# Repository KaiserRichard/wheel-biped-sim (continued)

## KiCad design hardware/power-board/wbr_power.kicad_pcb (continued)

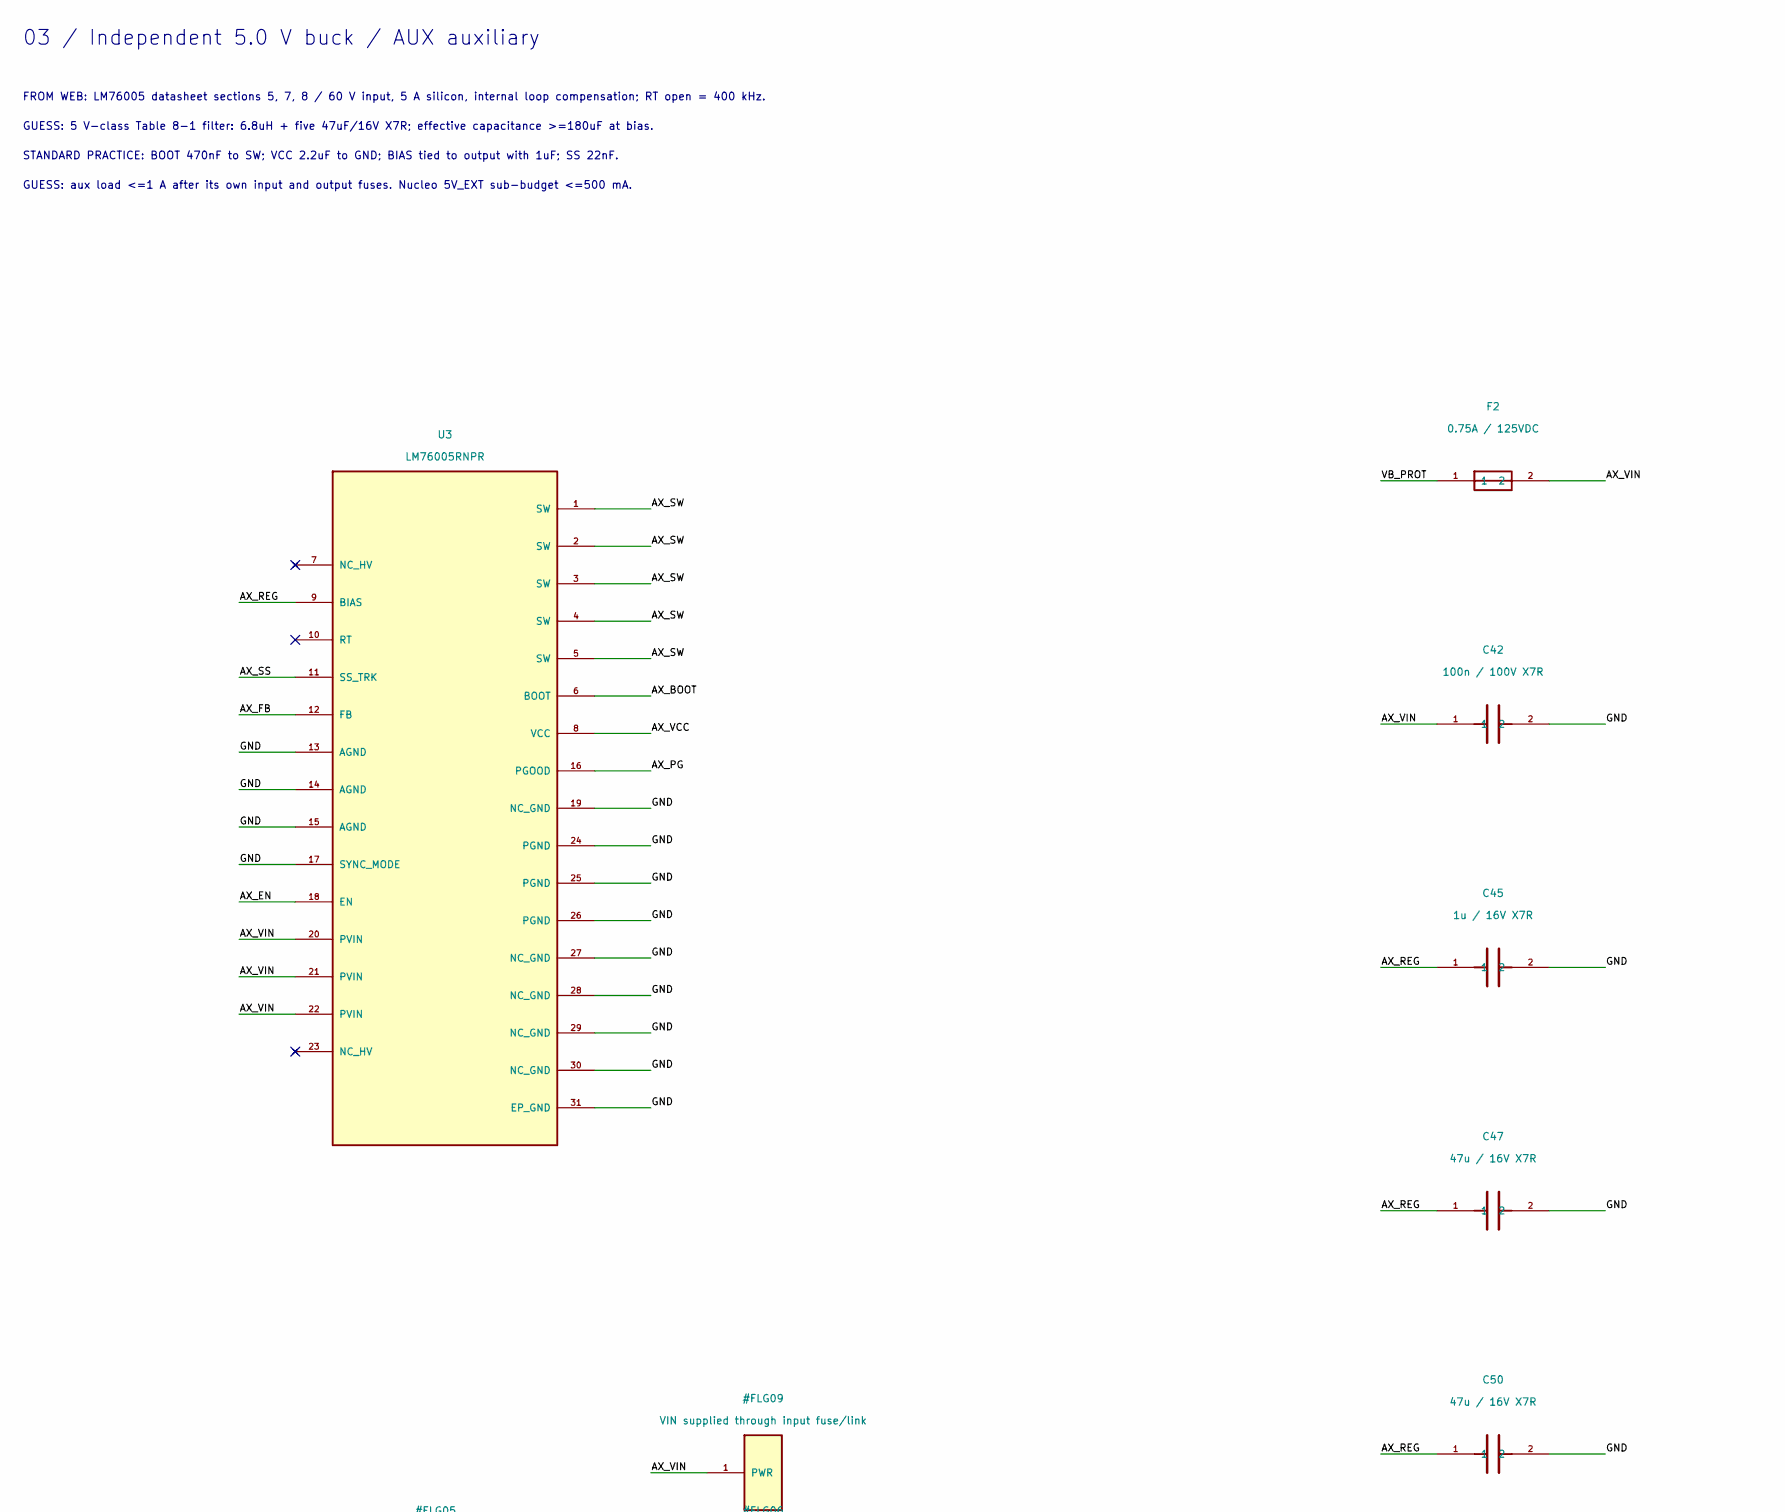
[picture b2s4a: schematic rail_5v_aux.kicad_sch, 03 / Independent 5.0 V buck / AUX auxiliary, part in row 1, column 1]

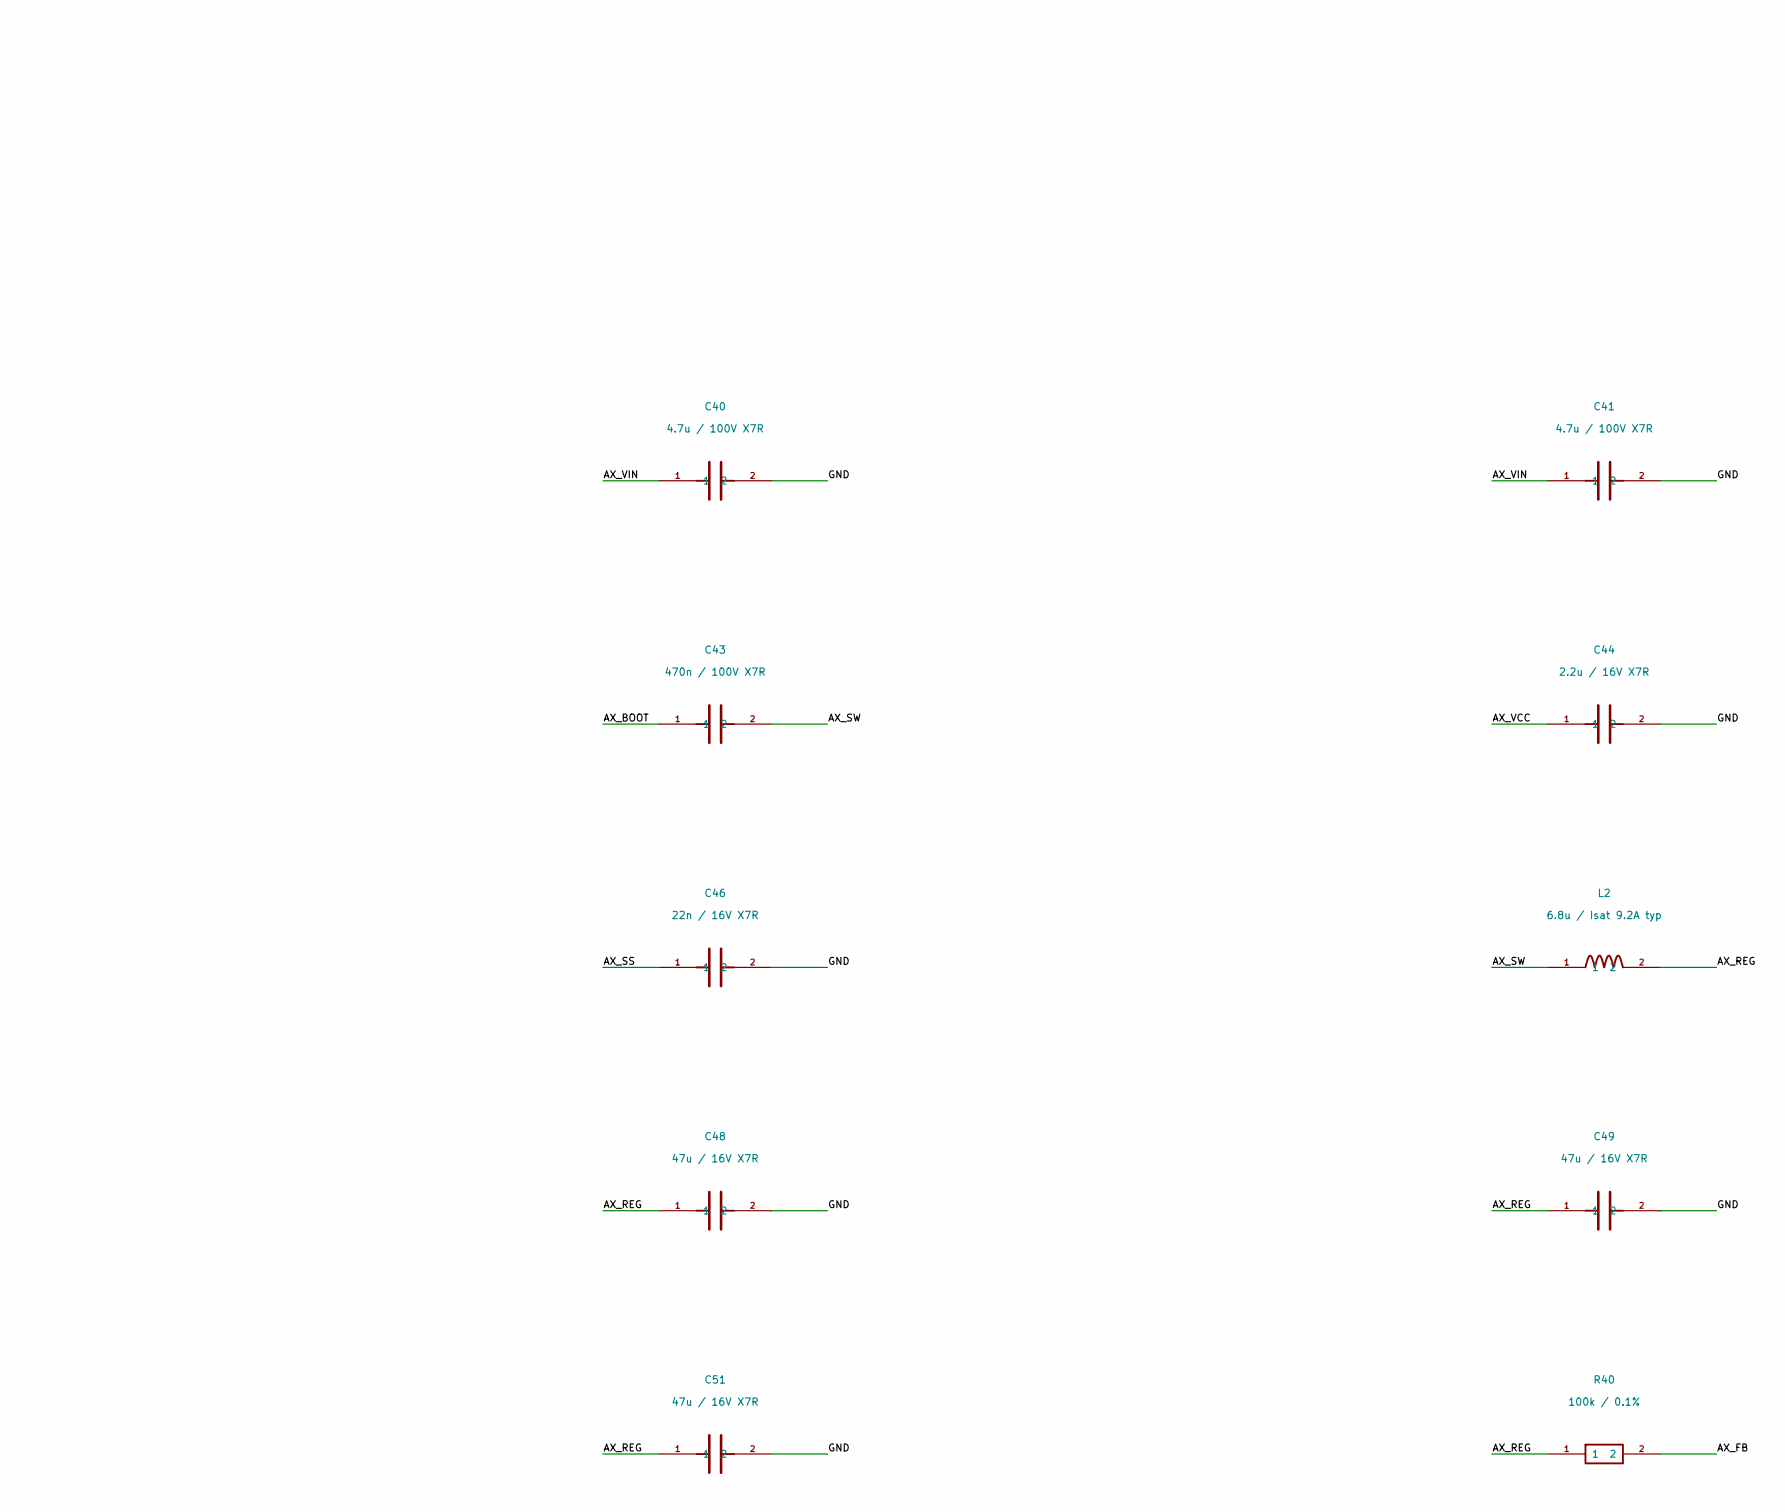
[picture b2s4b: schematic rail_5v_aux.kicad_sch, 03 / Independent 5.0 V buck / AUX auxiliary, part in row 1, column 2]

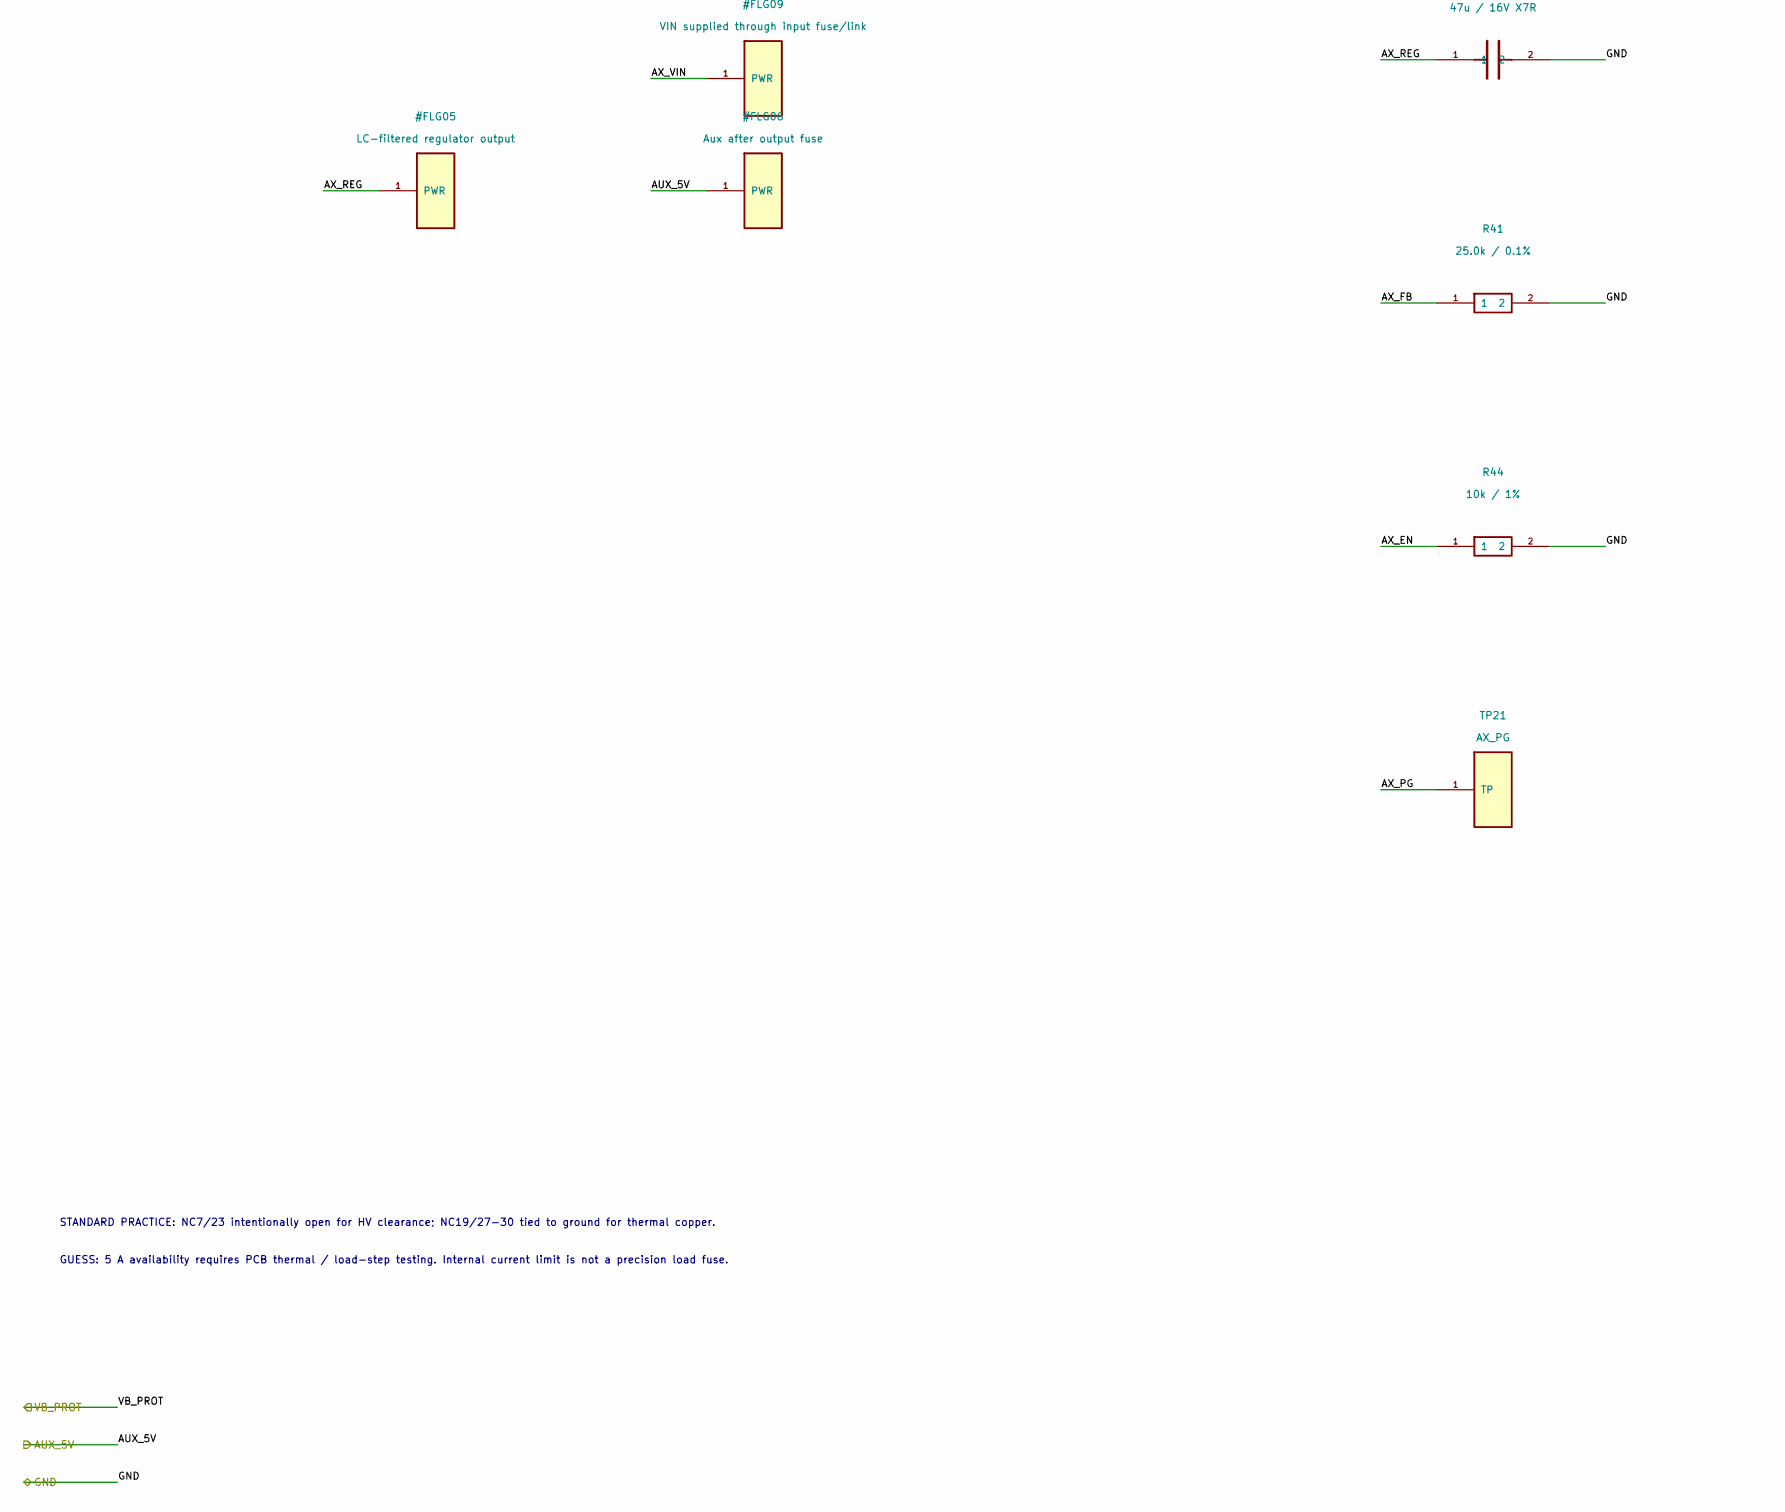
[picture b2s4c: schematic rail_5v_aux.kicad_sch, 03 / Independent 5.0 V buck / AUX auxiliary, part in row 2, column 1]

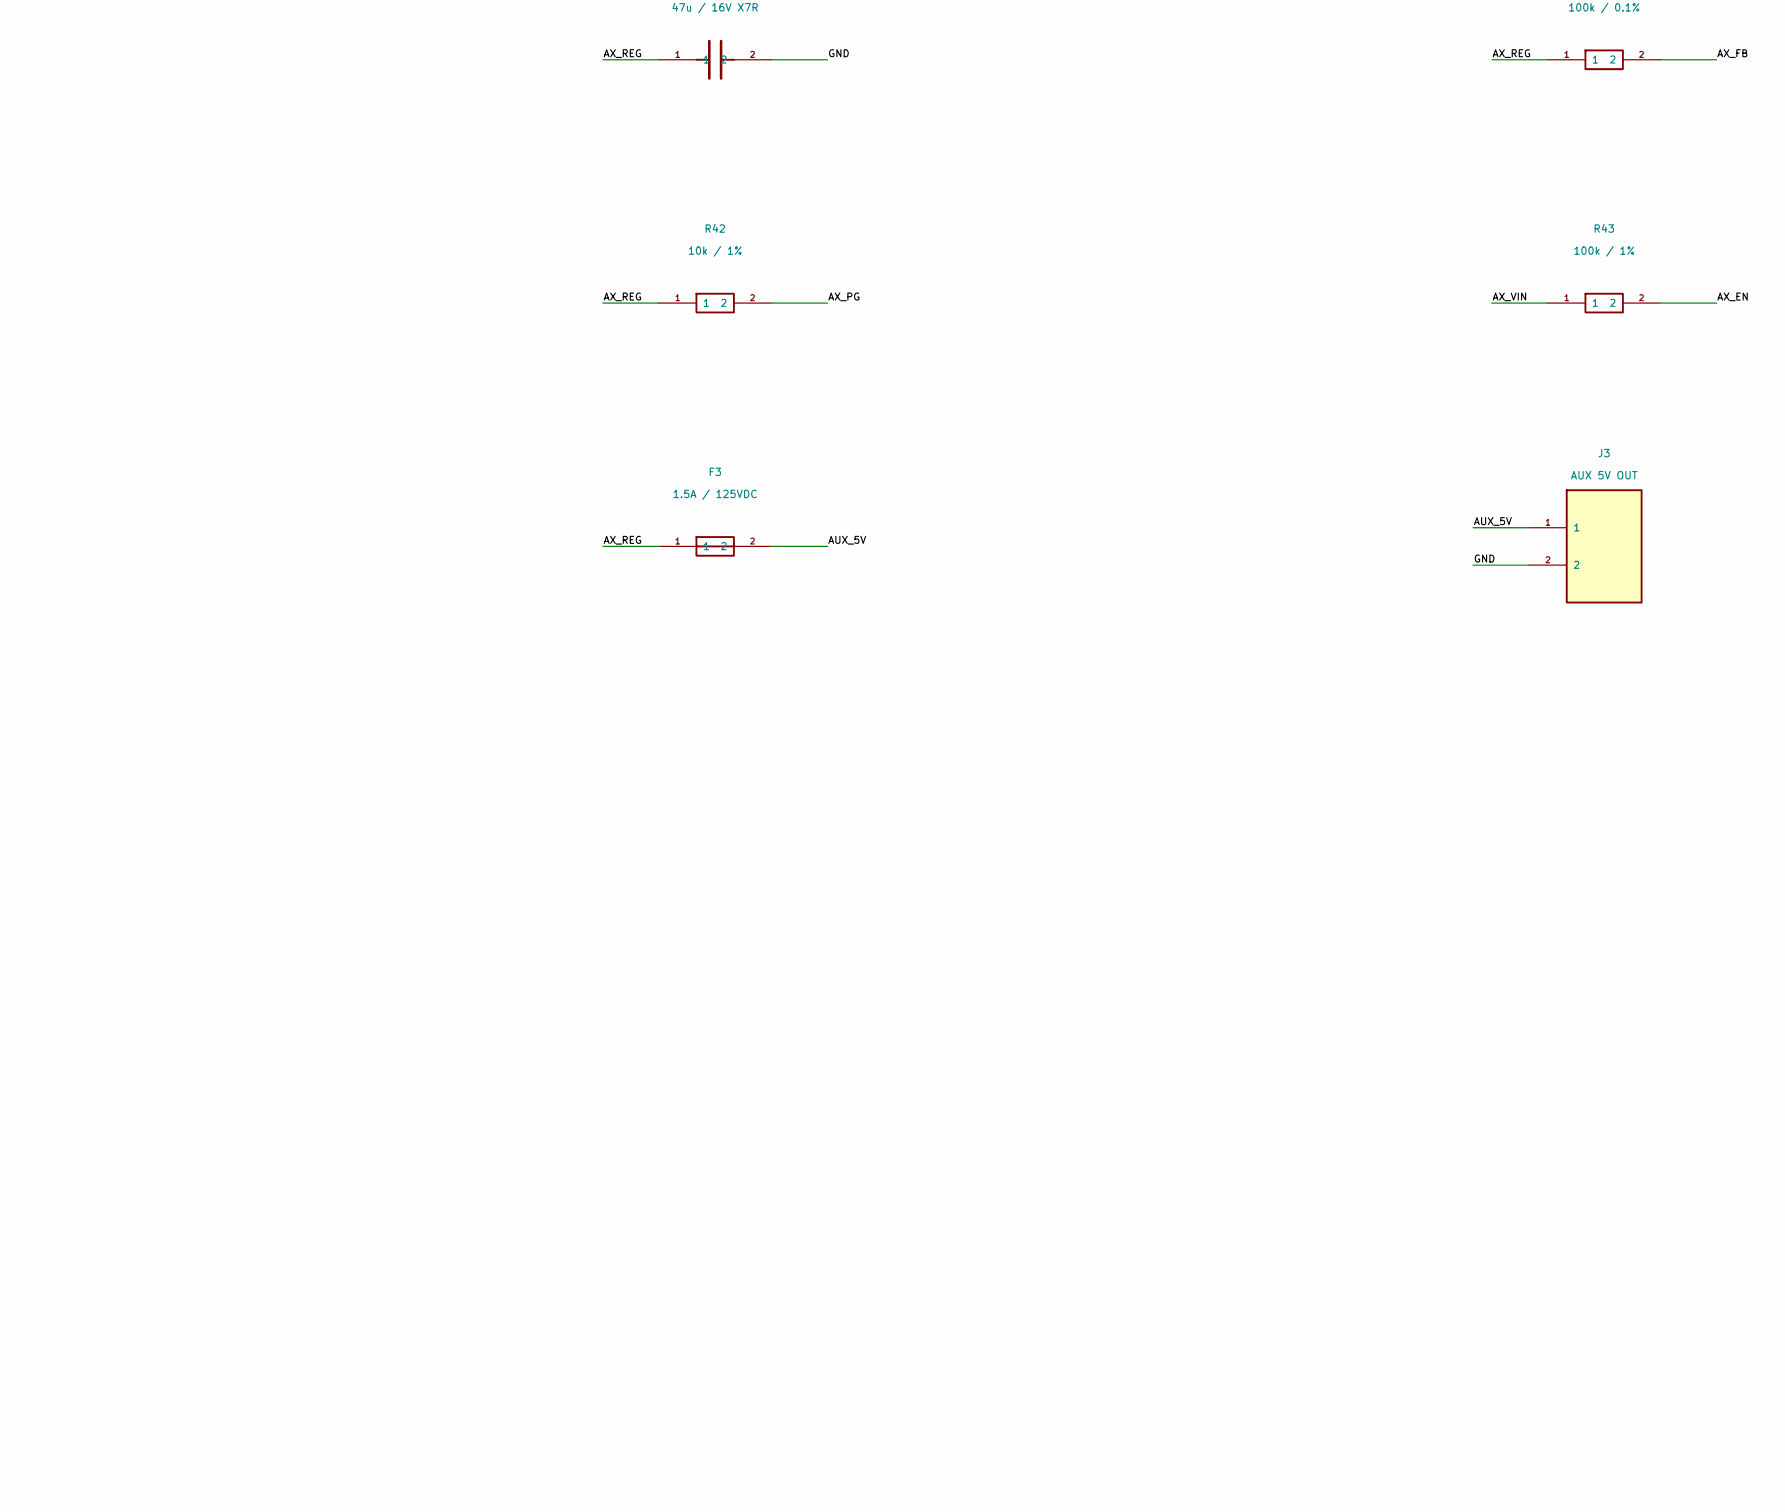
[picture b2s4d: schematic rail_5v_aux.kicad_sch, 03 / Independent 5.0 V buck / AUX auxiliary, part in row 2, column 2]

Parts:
C40, C41: 4.7u / 100V X7R; C_1210_3225Metric; Rating 100 V; verify effective capacitance; MPN 4.7u / 100V X7R
C42: 100n / 100V X7R; C_1210_3225Metric; Rating 100 V; MPN 100n / 100V X7R
C43: 470n / 100V X7R; C_1210_3225Metric; Rating 100 V; bootstrap floats at battery SW n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; MPN 470n / 100V X7R
C44: 2.2u / 16V X7R; C_0805_2012Metric; Rating 16 V; VCC decoupling; MPN 2.2u / 16V X7R
C45: 1u / 16V X7R; C_0805_2012Metric; Rating 16 V; BIAS decoupling; MPN 1u / 16V X7R
C46: 22n / 16V X7R; C_0805_2012Metric; Rating 16 V; ~11ms programmable soft-start; MPN 22n / 16V X7R
C47, C48, C49, C50, C51: 47u / 16V X7R; C_1210_3225Metric; Rating 16 V; five total >=180uF effective; MPN 47u / 16V X7R
F2: 0.75A / 125VDC; Fuse_Littelfuse-NANO2-451_453; Rating 125 VDC / board converter branch; MPN Littelfuse 0451.750MRL
F3: 1.5A / 125VDC; Fuse_Littelfuse-NANO2-451_453; Rating 125 VDC; 50 A interrupt; board aux outp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; MPN Littelfuse 045101.5MRL
J3: AUX 5V OUT; Molex_Micro-Fit_3.0_43045-0200_2x01_P3.00mm_Horizontal; Rating 250 V; >=3 A; MPN AUX 5V OUT
L2: 6.8u / Isat 9.2A typ; L_Coilcraft_XAL6060-XXX; Rating 60 V operating; Irms 7.0 A / 20 C rise;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; MPN Coilcraft XAL6060-682MEC
R40: 100k / 0.1%; R_0805_2012Metric; Rating 100 V; MPN 100k / 0.1%
R41: 25.0k / 0.1%; R_0805_2012Metric; Rating 100 V; MPN 25.0k / 0.1%
R42: 10k / 1%; R_0805_2012Metric; Rating 100 V; open-drain pull-up; MPN 10k / 1%
R43: 100k / 1%; R_1206_3216Metric; Rating 150 V; MPN 100k / 1%
R44: 10k / 1%; R_1206_3216Metric; Rating 150 V; MPN 10k / 1%
TP21: AX_PG; TestPoint_Pad_D2.0mm; Rating 5 V class PGOOD; not 3.3 V GPIO; MPN AX_PG
U3: LM76005RNPR; Texas_RNP0030B_WQFN-30-1EP_4x6mm_P0.5mm_EP1.8x4.5mm_Thermal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; Rating PVIN 60 V operating; 65 V absolute; 5 A; MPN LM76005RNPR

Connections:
/AUX_5V: F3.2, J3.1; also elsewhere on the board
/GND: C40.2, C41.2, C42.2, C44.2, C45.2, C46.2, C47.2, C48.2, C49.2, C50.2, C51.2, J3.2, R41.2, R44.2, U3.13 (AGND), U3.14 (AGND), U3.15 (AGND), U3.17 (SYNC_MODE), U3.19 (NC_GND), U3.24 (PGND), U3.25 (PGND), U3.26 (PGND), U3.27 (NC_GND), U3.28 (NC_GND), U3.29 (NC_GND), U3.30 (NC_GND), U3.31 (EP_GND); also elsewhere on the board
/VB_PROT: F2.1; also elsewhere on the board
/rail_5v_aux/AX_BOOT: C43.1, U3.6 (BOOT)
/rail_5v_aux/AX_EN: R43.2, R44.1, U3.18 (EN)
/rail_5v_aux/AX_FB: R40.2, R41.1, U3.12 (FB)
/rail_5v_aux/AX_PG: R42.2, TP21.1, U3.16 (PGOOD)
/rail_5v_aux/AX_REG: C45.1, C47.1, C48.1, C49.1, C50.1, C51.1, F3.1, L2.2, R40.1, R42.1, U3.9 (BIAS)
/rail_5v_aux/AX_SS: C46.1, U3.11 (SS_TRK)
/rail_5v_aux/AX_SW: C43.2, L2.1, U3.1 (SW), U3.2 (SW), U3.3 (SW), U3.4 (SW), U3.5 (SW)
/rail_5v_aux/AX_VCC: C44.1, U3.8 (VCC)
/rail_5v_aux/AX_VIN: C40.1, C41.1, C42.1, F2.2, R43.1, U3.20 (PVIN), U3.21 (PVIN), U3.22 (PVIN)

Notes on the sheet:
03 / Independent 5.0 V buck / AUX auxiliary
FROM WEB: LM76005 datasheet sections 5, 7, 8 / 60 V input, 5 A silicon, internal loop compensation; RT open = 400 kHz.
GUESS: 5 V-class Table 8-1 filter: 6.8uH + five 47uF/16V X7R; effective capacitance >=180uF at bias.
STANDARD PRACTICE: BOOT 470nF to SW; VCC 2.2uF to GND; BIAS tied to output with 1uF; SS 22nF.
GUESS: aux load <=1 A after its own input and output fuses. Nucleo 5V_EXT sub-budget <=500 mA.
STANDARD PRACTICE: NC7/23 intentionally open for HV clearance; NC19/27-30 tied to ground for thermal copper.
GUESS: 5 A availability requires PCB thermal / load-step testing. Internal current limit is not a precision load fuse.
